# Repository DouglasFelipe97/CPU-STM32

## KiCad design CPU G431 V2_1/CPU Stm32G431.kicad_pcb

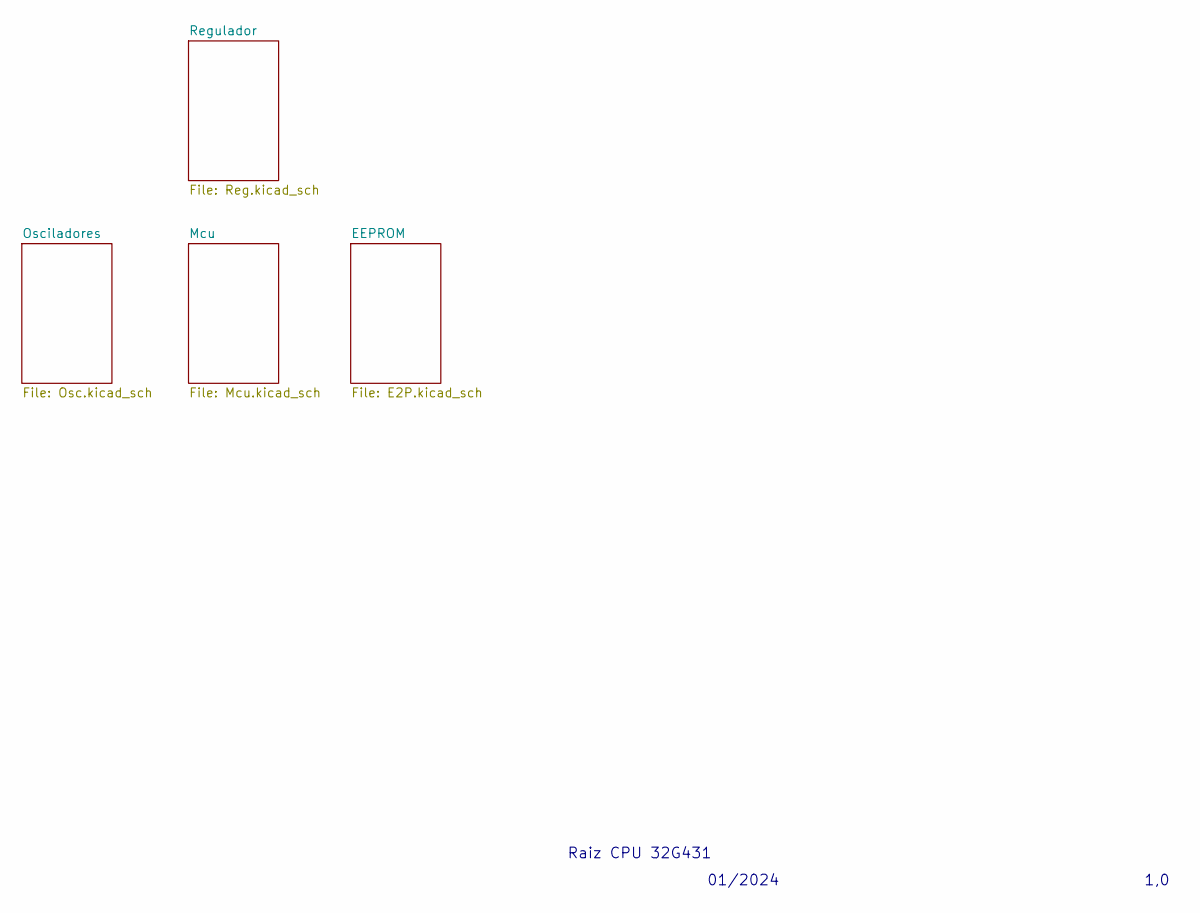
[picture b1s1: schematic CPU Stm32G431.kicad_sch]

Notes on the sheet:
Raiz CPU 32G431
01/2024
1,0

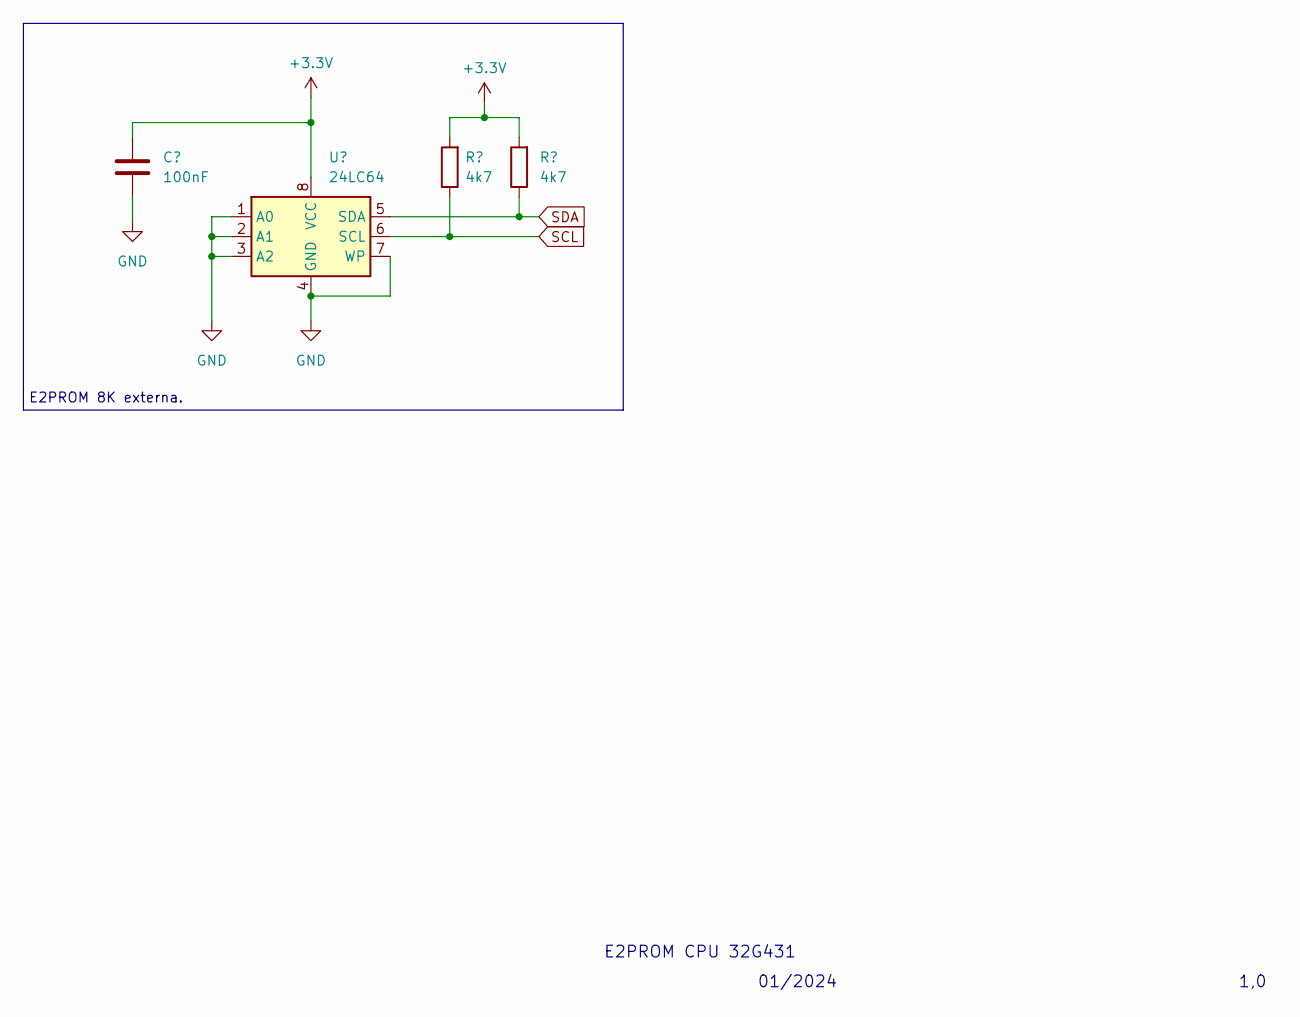
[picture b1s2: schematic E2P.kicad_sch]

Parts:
C6: 100nF; C_0805_2012Metric_Pad1.18x1.45mm_HandSolder
R6, R7: 4k7; R_0805_2012Metric_Pad1.20x1.40mm_HandSolder
U2: 24LC64; SOIC-8_3.9x4.9mm_P1.27mm

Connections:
GND: C6.1, U2.1 (A0), U2.2 (A1), U2.3 (A2), U2.4 (GND), U2.7 (WP); also elsewhere on the board
SCL: R6.1, U2.6 (SCL); also elsewhere on the board
SDA: R7.1, U2.5 (SDA); also elsewhere on the board
VDD: C6.2, R6.2, R7.2, U2.8 (VCC); also elsewhere on the board

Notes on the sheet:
E2PROM 8K externa.
E2PROM CPU 32G431
1,0
01/2024

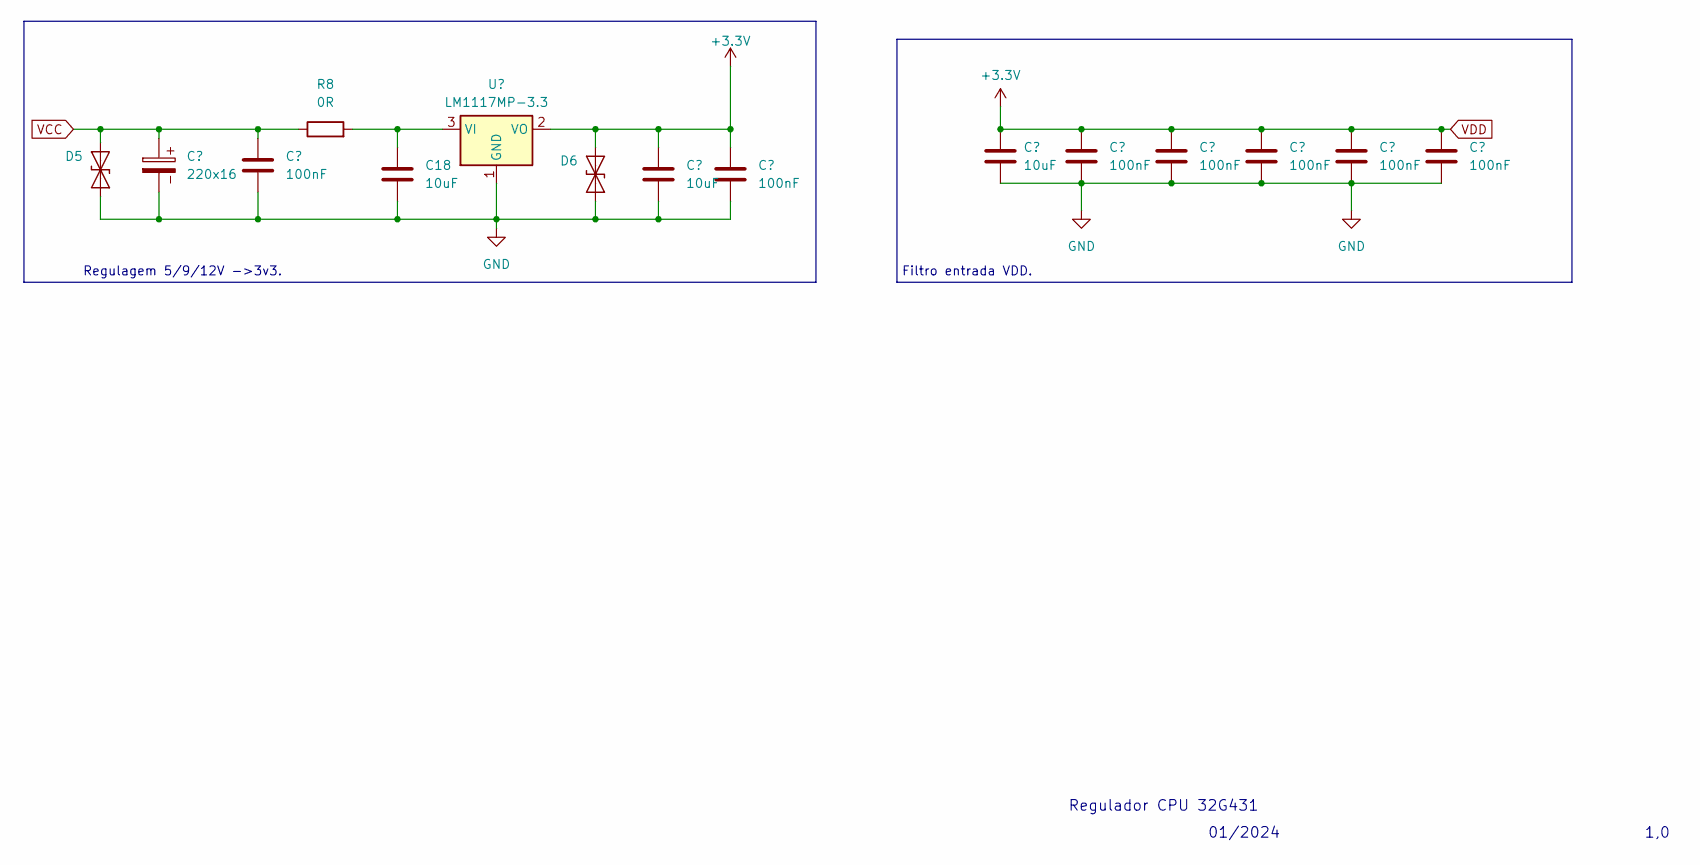
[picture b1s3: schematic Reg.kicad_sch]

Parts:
C7: 220x16; CP_Radial_D5.0mm_P2.50mm
C8, C10, C12, C13, C14, C15, C16: 100nF; C_0805_2012Metric_Pad1.18x1.45mm_HandSolder
C9, C11, C18: 10uF; C_0805_2012Metric_Pad1.18x1.45mm_HandSolder
D5: SMAJ6.5CA; D_SMA
D6: SMAJ6.5CA; D_MiniMELF
R8: 0R; R_0805_2012Metric_Pad1.20x1.40mm_HandSolder
U3: LM1117MP-3.3; SOT-223-3_TabPin2

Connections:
GND: C7.2, C8.1, C9.1, C10.1, C11.1, C12.1, C13.1, C14.1, C15.1, C16.1, C18.1, D5.1 (A1), D6.1 (A1), U3.1 (GND); also elsewhere on the board
unnamed: C18.2, R8.2, U3.3 (VI)
VCC: C7.1, C8.2, D5.2 (A2), R8.1; also elsewhere on the board
VDD: C9.2, C10.2, C11.2, C12.2, C13.2, C14.2, C15.2, C16.2, D6.2 (A2), U3.2 (VO); also elsewhere on the board

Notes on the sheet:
Regulagem 5/9/12V ->3v3.
01/2024
Regulador CPU 32G431
1,0
Filtro entrada VDD.

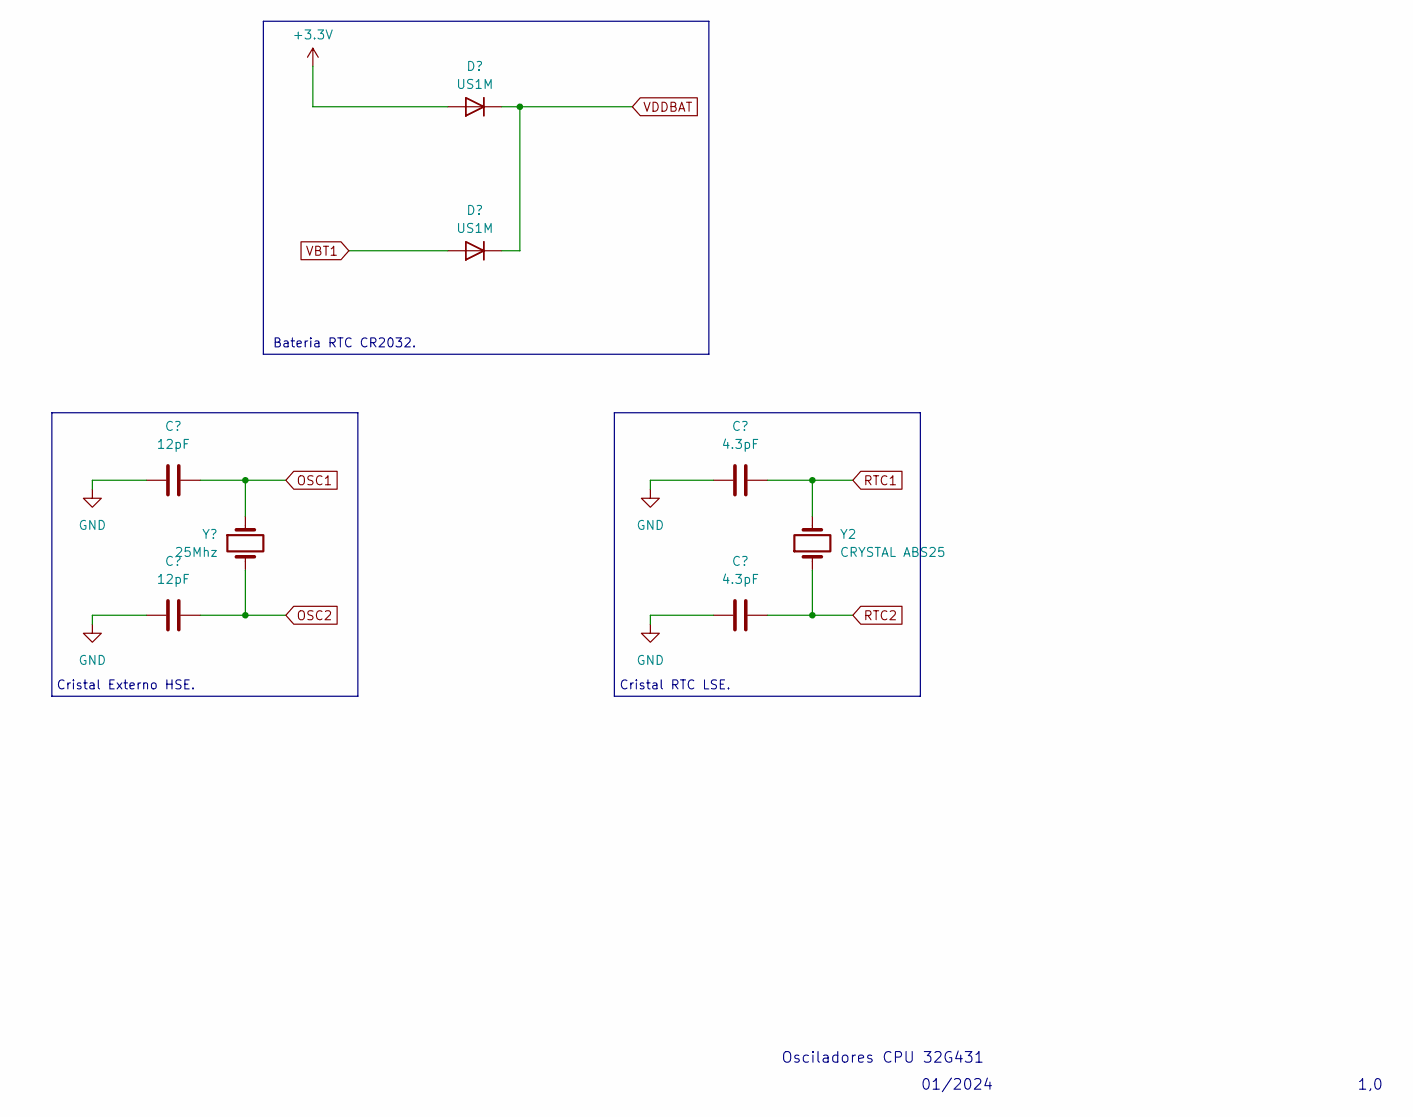
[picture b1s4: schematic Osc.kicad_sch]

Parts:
C2, C3: 12pF; C_0805_2012Metric_Pad1.18x1.45mm_HandSolder
C4, C5: 4.3pF; C_0805_2012Metric_Pad1.18x1.45mm_HandSolder
D3, D4: US1M; D_SMA
Y1: 25Mhz; Crystal_HC49-4H_Vertical
Y2: CRYSTAL ABS25; Crystal_SMD_Abracon_ABS25 Vertical

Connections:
GND: C2.1, C3.1, C4.1, C5.1; also elsewhere on the board
OSC1: C2.2, Y1.1; also elsewhere on the board
OSC2: C3.2, Y1.2; also elsewhere on the board
RTC1: C4.2, Y2.2; also elsewhere on the board
RTC2: C5.2, Y2.1; also elsewhere on the board
VBT1: D4.2 (A); also elsewhere on the board
VDD: D3.2 (A); also elsewhere on the board
VDDBAT: D3.1 (K), D4.1 (K); also elsewhere on the board

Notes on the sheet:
1,0
Cristal RTC LSE.
01/2024
Bateria RTC CR2032.
Cristal Externo HSE.
Osciladores CPU 32G431

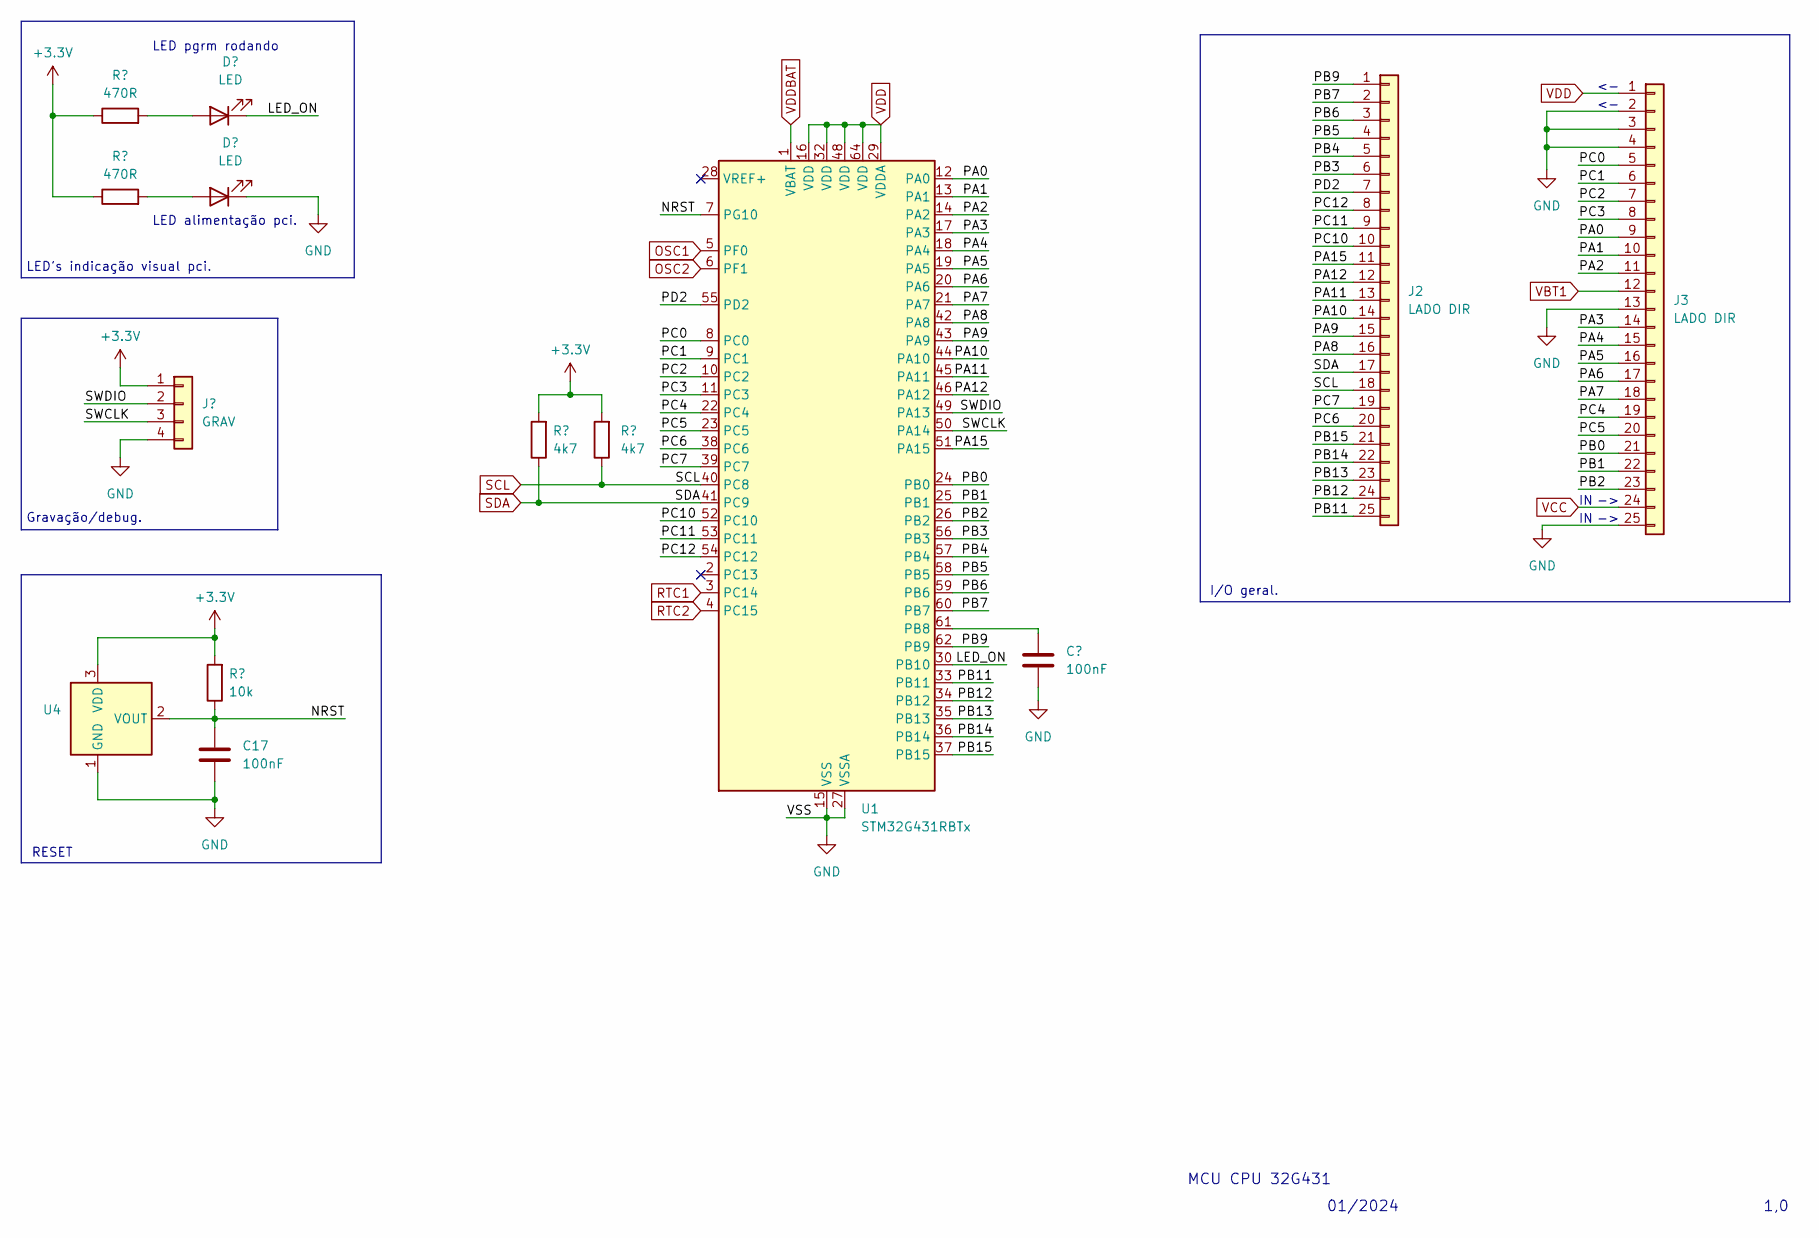
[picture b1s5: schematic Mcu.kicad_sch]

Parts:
C1, C17: 100nF; C_0805_2012Metric_Pad1.18x1.45mm_HandSolder
D1, D2: LED; LED_0805_2012Metric_Pad1.15x1.40mm_HandSolder
J1: GRAV; PinHeader_1x04_P2.54mm_Vertical
J2, J3: LADO DIR; PinHeader_1x25_P2.54mm_Vertical
R1: 10k; R_0805_2012Metric_Pad1.20x1.40mm_HandSolder
R2, R3: 470R; R_0805_2012Metric_Pad1.20x1.40mm_HandSolder
R4, R5: 4k7; R_0805_2012Metric_Pad1.20x1.40mm_HandSolder
U1: STM32G431RBTx; LQFP-64_10x10mm_P0.5mm
U4: BD48KxxG; SOT-23

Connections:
/Mcu/LED_ON: D1.1 (K), U1.30 (PB10)
/Mcu/NRST: C17.2, R1.1, U1.7 (PG10), U4.2 (VOUT)
/Mcu/PA0: J3.9, U1.12 (PA0)
/Mcu/PA1: J3.10, U1.13 (PA1)
/Mcu/PA2: J3.11, U1.14 (PA2)
/Mcu/PA3: J3.14, U1.17 (PA3)
/Mcu/PA4: J3.15, U1.18 (PA4)
/Mcu/PA5: J3.16, U1.19 (PA5)
/Mcu/PA6: J3.17, U1.20 (PA6)
/Mcu/PA7: J3.18, U1.21 (PA7)
/Mcu/PA8: J2.16, U1.42 (PA8)
/Mcu/PA9: J2.15, U1.43 (PA9)
/Mcu/PA10: J2.14, U1.44 (PA10)
/Mcu/PA11: J2.13, U1.45 (PA11)
/Mcu/PA12: J2.12, U1.46 (PA12)
/Mcu/PA15: J2.11, U1.51 (PA15)
/Mcu/PB0: J3.21, U1.24 (PB0)
/Mcu/PB1: J3.22, U1.25 (PB1)
/Mcu/PB2: J3.23, U1.26 (PB2)
/Mcu/PB3: J2.6, U1.56 (PB3)
/Mcu/PB4: J2.5, U1.57 (PB4)
/Mcu/PB5: J2.4, U1.58 (PB5)
/Mcu/PB6: J2.3, U1.59 (PB6)
/Mcu/PB7: J2.2, U1.60 (PB7)
/Mcu/PB9: J2.1, U1.62 (PB9)
/Mcu/PB11: J2.25, U1.33 (PB11)
/Mcu/PB12: J2.24, U1.34 (PB12)
/Mcu/PB13: J2.23, U1.35 (PB13)
/Mcu/PB14: J2.22, U1.36 (PB14)
/Mcu/PB15: J2.21, U1.37 (PB15)
/Mcu/PC0: J3.5, U1.8 (PC0)
/Mcu/PC1: J3.6, U1.9 (PC1)
/Mcu/PC2: J3.7, U1.10 (PC2)
/Mcu/PC3: J3.8, U1.11 (PC3)
/Mcu/PC4: J3.19, U1.22 (PC4)
/Mcu/PC5: J3.20, U1.23 (PC5)
/Mcu/PC6: J2.20, U1.38 (PC6)
/Mcu/PC7: J2.19, U1.39 (PC7)
/Mcu/PC10: J2.10, U1.52 (PC10)
/Mcu/PC11: J2.9, U1.53 (PC11)
/Mcu/PC12: J2.8, U1.54 (PC12)
/Mcu/PD2: J2.7, U1.55 (PD2)
/Mcu/SWCLK: J1.3, U1.50 (PA14)
/Mcu/SWDIO: J1.2, U1.49 (PA13)
GND: C1.1, C17.1, D2.1 (K), J1.4, J3.2, J3.3, J3.4, J3.13, J3.25, U1.15 (VSS), U1.27 (VSSA), U1.31 (VSS), U1.47 (VSS), U1.63 (VSS), U4.1 (GND); also elsewhere on the board
unnamed: D1.2 (A), R2.2
unnamed: D2.2 (A), R3.2
unnamed: C1.2, U1.61 (PB8)
OSC1: U1.5 (PF0); also elsewhere on the board
OSC2: U1.6 (PF1); also elsewhere on the board
RTC1: U1.3 (PC14); also elsewhere on the board
RTC2: U1.4 (PC15); also elsewhere on the board
SCL: J2.18, R5.1, U1.40 (PC8); also elsewhere on the board
SDA: J2.17, R4.1, U1.41 (PC9); also elsewhere on the board
VBT1: J3.12; also elsewhere on the board
VCC: J3.24; also elsewhere on the board
VDD: J1.1, J3.1, R1.2, R2.1, R3.1, R4.2, R5.2, U1.16 (VDD), U1.29 (VDDA), U1.32 (VDD), U1.48 (VDD), U1.64 (VDD), U4.3 (VDD); also elsewhere on the board
VDDBAT: U1.1 (VBAT); also elsewhere on the board

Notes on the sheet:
LED alimentação pci.
LED's indicação visual pci.
1,0
I/O geral.
01/2024
Gravação/debug.
LED pgrm rodando
RESET
MCU CPU 32G431

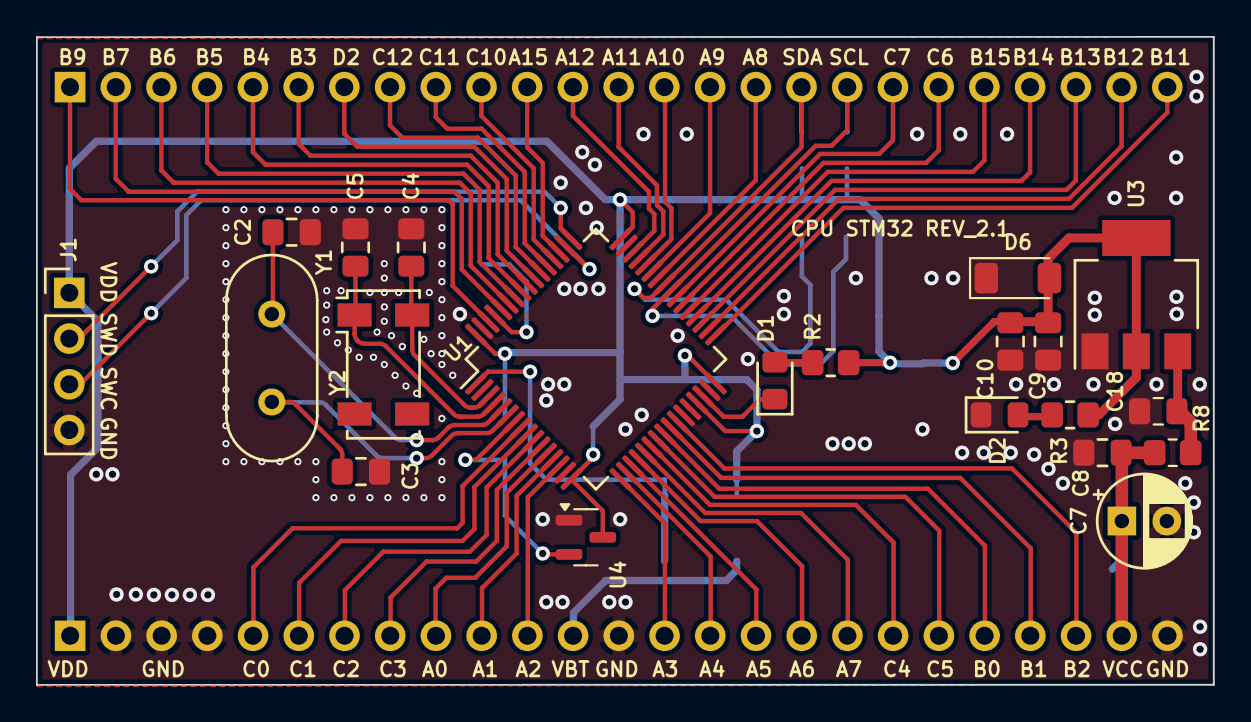
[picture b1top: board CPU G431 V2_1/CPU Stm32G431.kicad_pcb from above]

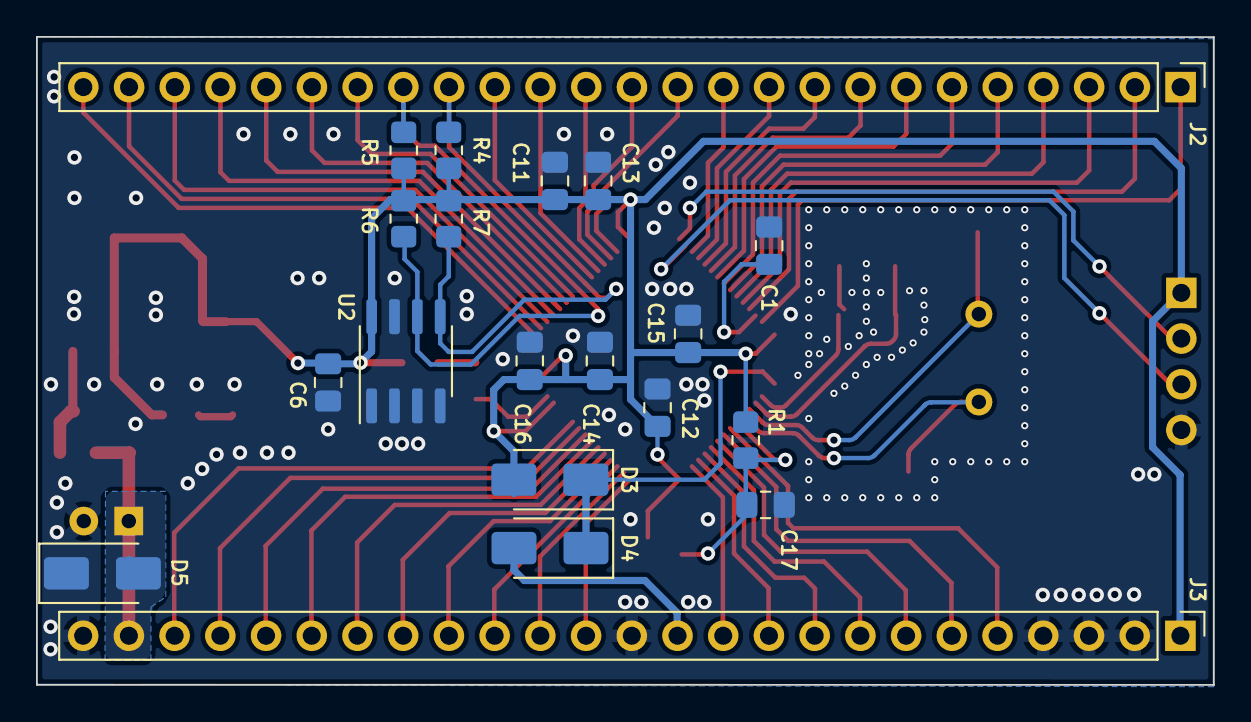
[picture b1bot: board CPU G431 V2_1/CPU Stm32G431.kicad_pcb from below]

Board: 2 copper layers, 65.4 x 36.0 mm, 41 parts (20 on the bottom side), 59 nets.

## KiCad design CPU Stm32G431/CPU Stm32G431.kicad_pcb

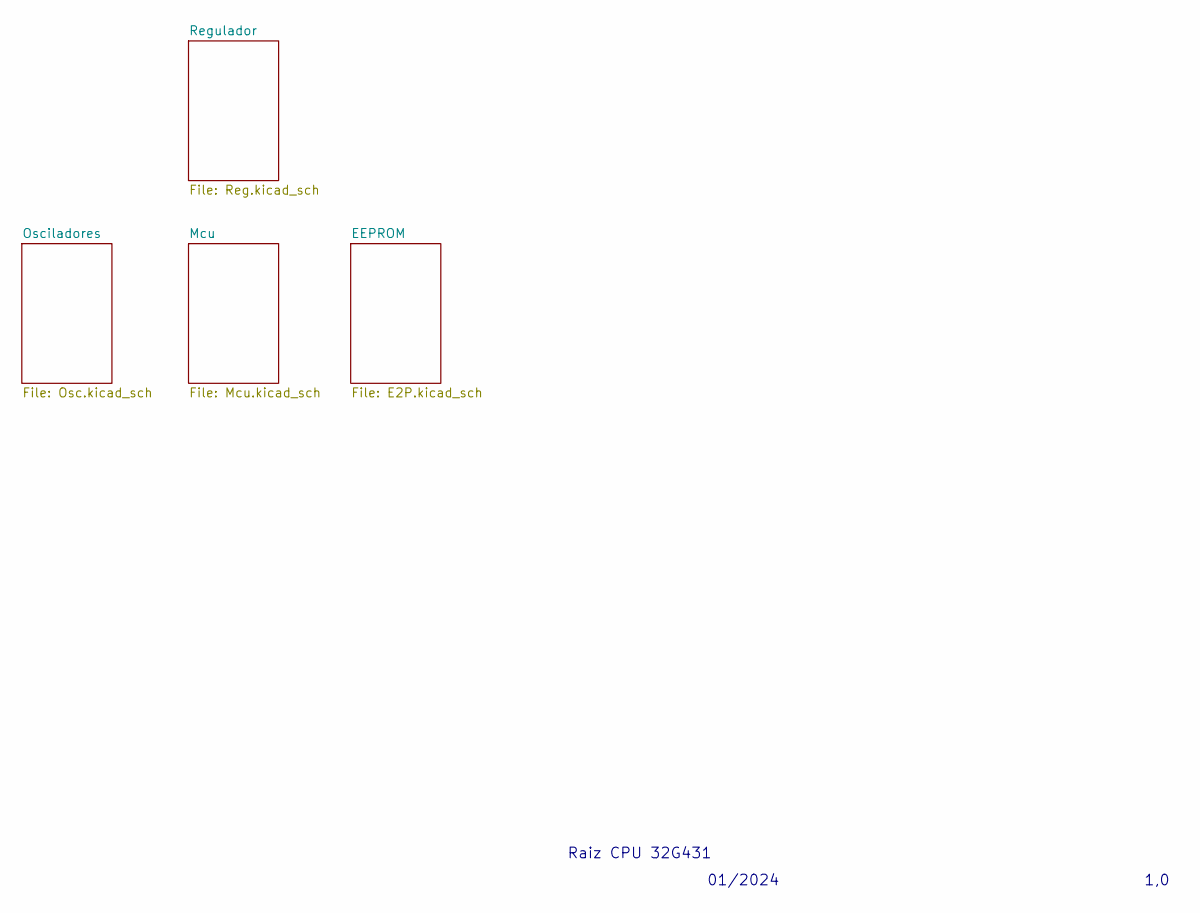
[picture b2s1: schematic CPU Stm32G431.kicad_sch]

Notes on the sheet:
Raiz CPU 32G431
01/2024
1,0

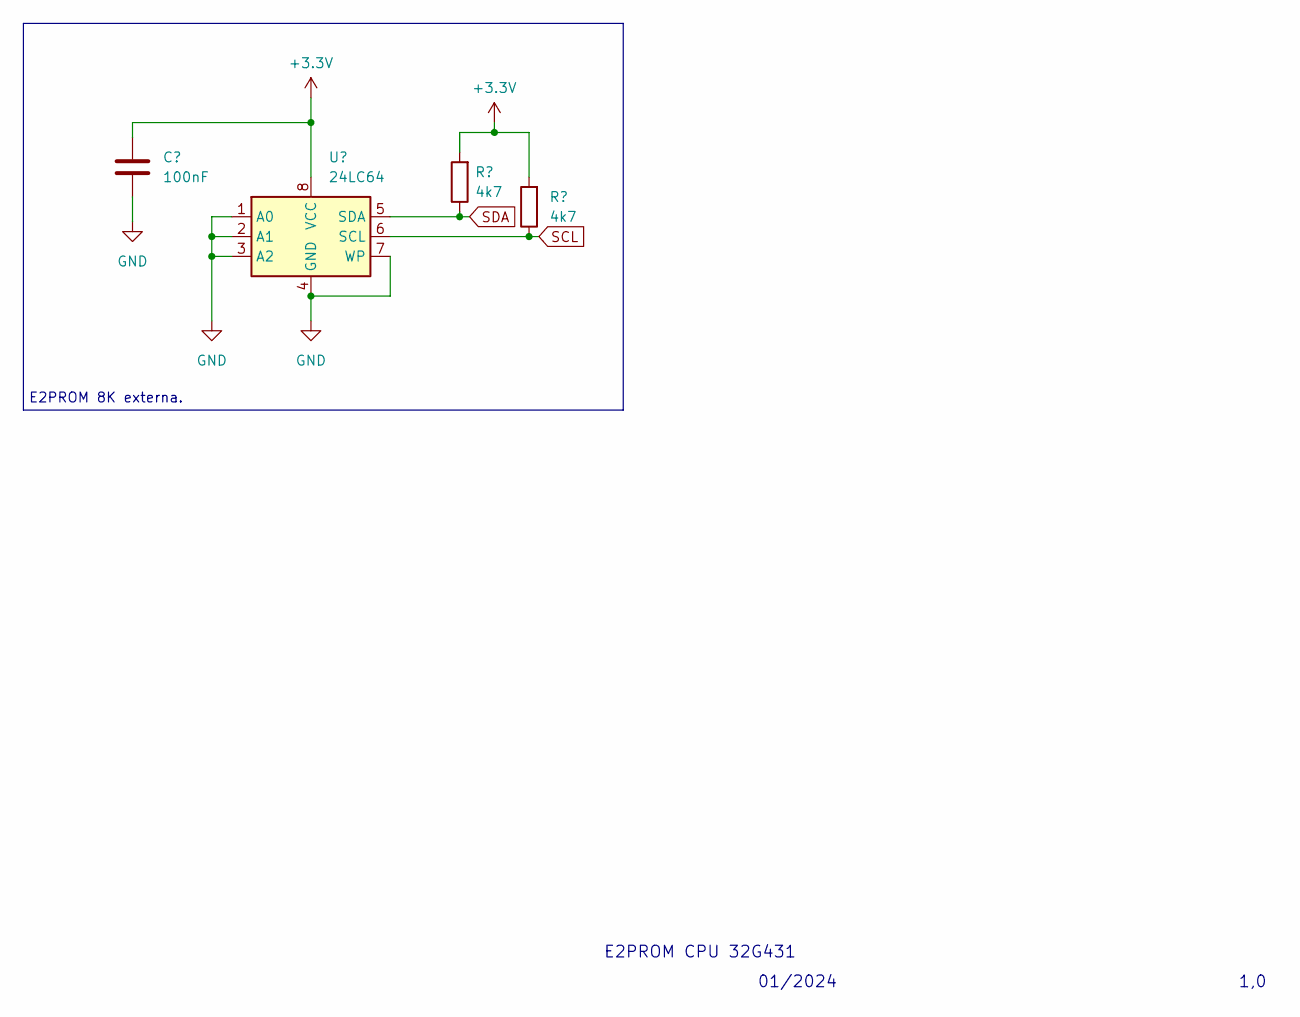
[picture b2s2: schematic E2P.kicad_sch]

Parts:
C17: 100nF; C_0805_2012Metric_Pad1.18x1.45mm_HandSolder
R4, R5: 4k7; R_0805_2012Metric_Pad1.20x1.40mm_HandSolder
U3: 24LC64; SOIC-8_3.9x4.9mm_P1.27mm

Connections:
GND: C17.1, U3.1 (A0), U3.2 (A1), U3.3 (A2), U3.4 (GND), U3.7 (WP); also elsewhere on the board
SCL: R5.1, U3.6 (SCL); also elsewhere on the board
SDA: R4.1, U3.5 (SDA); also elsewhere on the board
VDD: C17.2, R4.2, R5.2, U3.8 (VCC); also elsewhere on the board

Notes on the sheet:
E2PROM 8K externa.
E2PROM CPU 32G431
1,0
01/2024

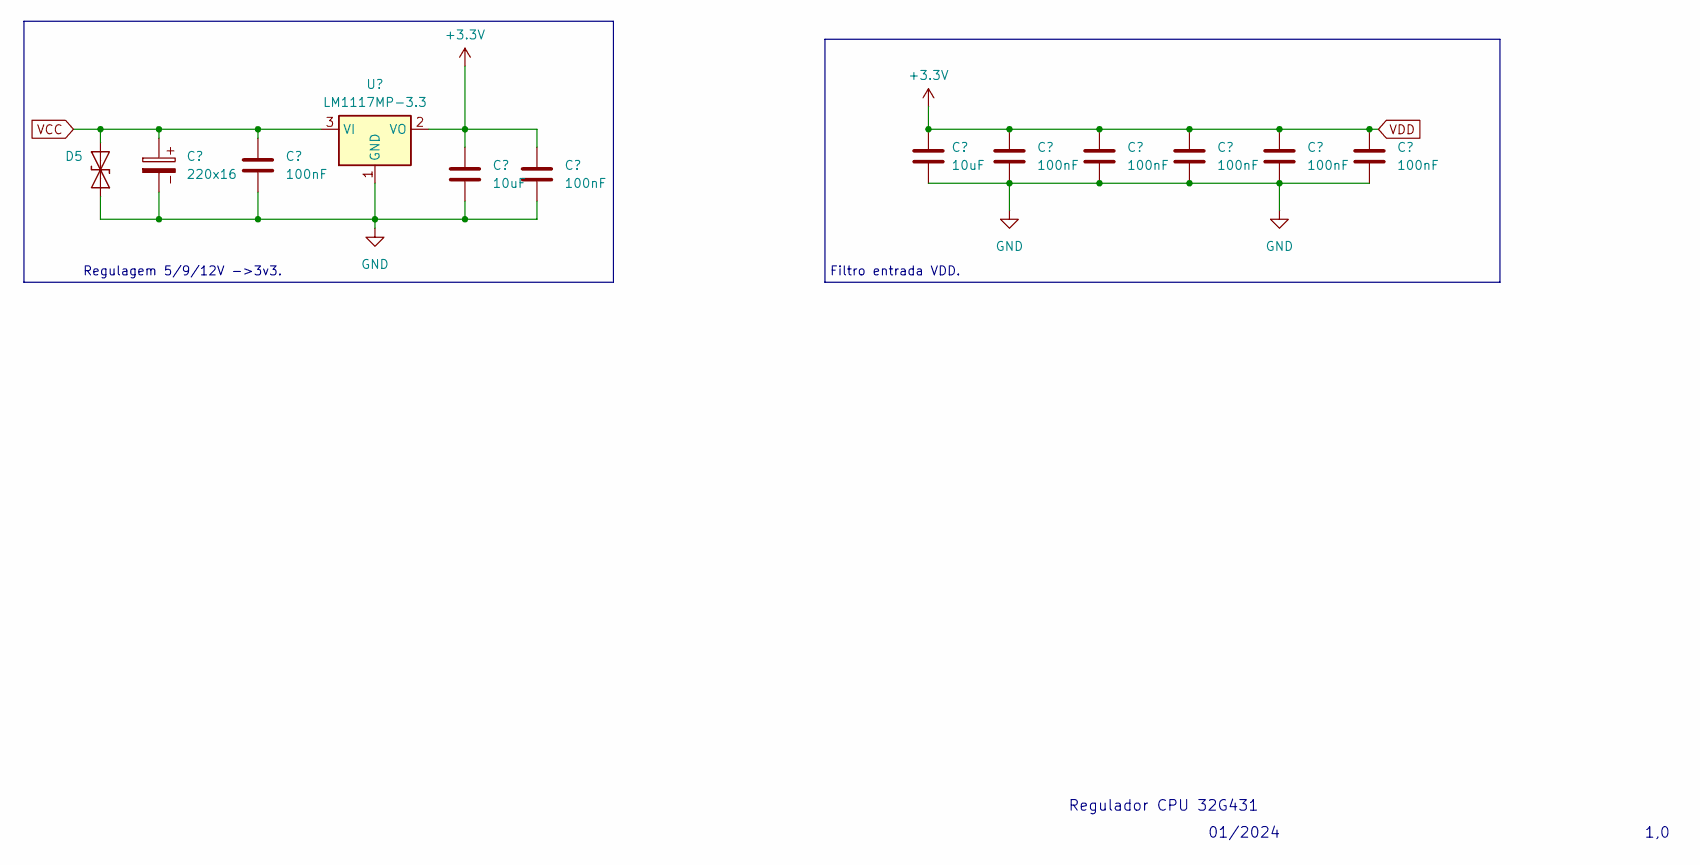
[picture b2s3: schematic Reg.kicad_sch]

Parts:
C5: 220x16; CP_Radial_D5.0mm_P2.50mm
C6, C8, C10, C11, C12, C13, C14: 100nF; C_0805_2012Metric_Pad1.18x1.45mm_HandSolder
C7, C9: 10uF; C_0805_2012Metric_Pad1.18x1.45mm_HandSolder
D5: SMAJ6.5CA; D_SMA
U1: LM1117MP-3.3; SOT-223-3_TabPin2

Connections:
GND: C5.2, C6.1, C7.1, C8.1, C9.1, C10.1, C11.1, C12.1, C13.1, C14.1, D5.1 (A1), U1.1 (GND); also elsewhere on the board
VCC: C5.1, C6.2, D5.2 (A2), U1.3 (VI); also elsewhere on the board
VDD: C7.2, C8.2, C9.2, C10.2, C11.2, C12.2, C13.2, C14.2, U1.2 (VO); also elsewhere on the board

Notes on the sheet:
Regulagem 5/9/12V ->3v3.
01/2024
Regulador CPU 32G431
1,0
Filtro entrada VDD.

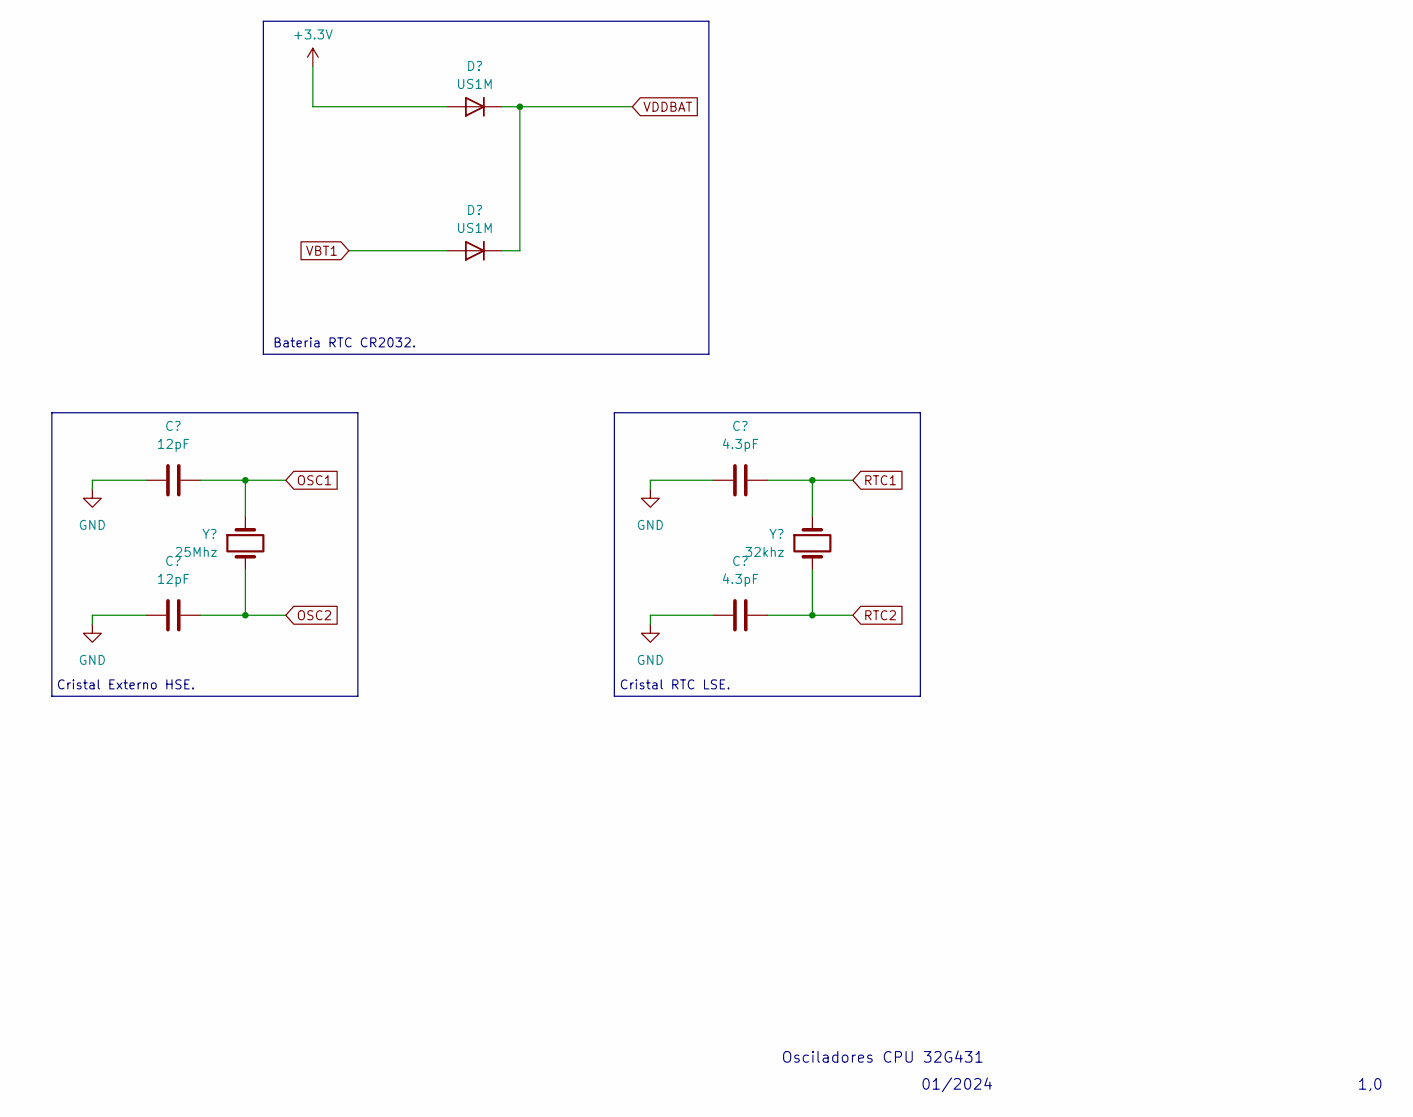
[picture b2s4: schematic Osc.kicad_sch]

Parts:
C1, C2: 12pF; C_0805_2012Metric_Pad1.18x1.45mm_HandSolder
C3, C4: 4.3pF; C_0805_2012Metric_Pad1.18x1.45mm_HandSolder
D1, D2: US1M; D_SMA
Y1: 25Mhz; Crystal_HC49-4H_Vertical
Y2: 32khz; Crystal_SMD_SeikoEpson_MC306-4Pin_8.0x3.2mm

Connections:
GND: C1.1, C2.1, C3.1, C4.1; also elsewhere on the board
OSC1: C1.2, Y1.1; also elsewhere on the board
OSC2: C2.2, Y1.2; also elsewhere on the board
RTC1: C3.2, Y2.1; also elsewhere on the board
RTC2: C4.2, Y2.2; also elsewhere on the board
VBT1: D2.2 (A); also elsewhere on the board
VDD: D1.2 (A); also elsewhere on the board
VDDBAT: D1.1 (K), D2.1 (K); also elsewhere on the board

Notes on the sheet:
1,0
Cristal RTC LSE.
01/2024
Bateria RTC CR2032.
Cristal Externo HSE.
Osciladores CPU 32G431

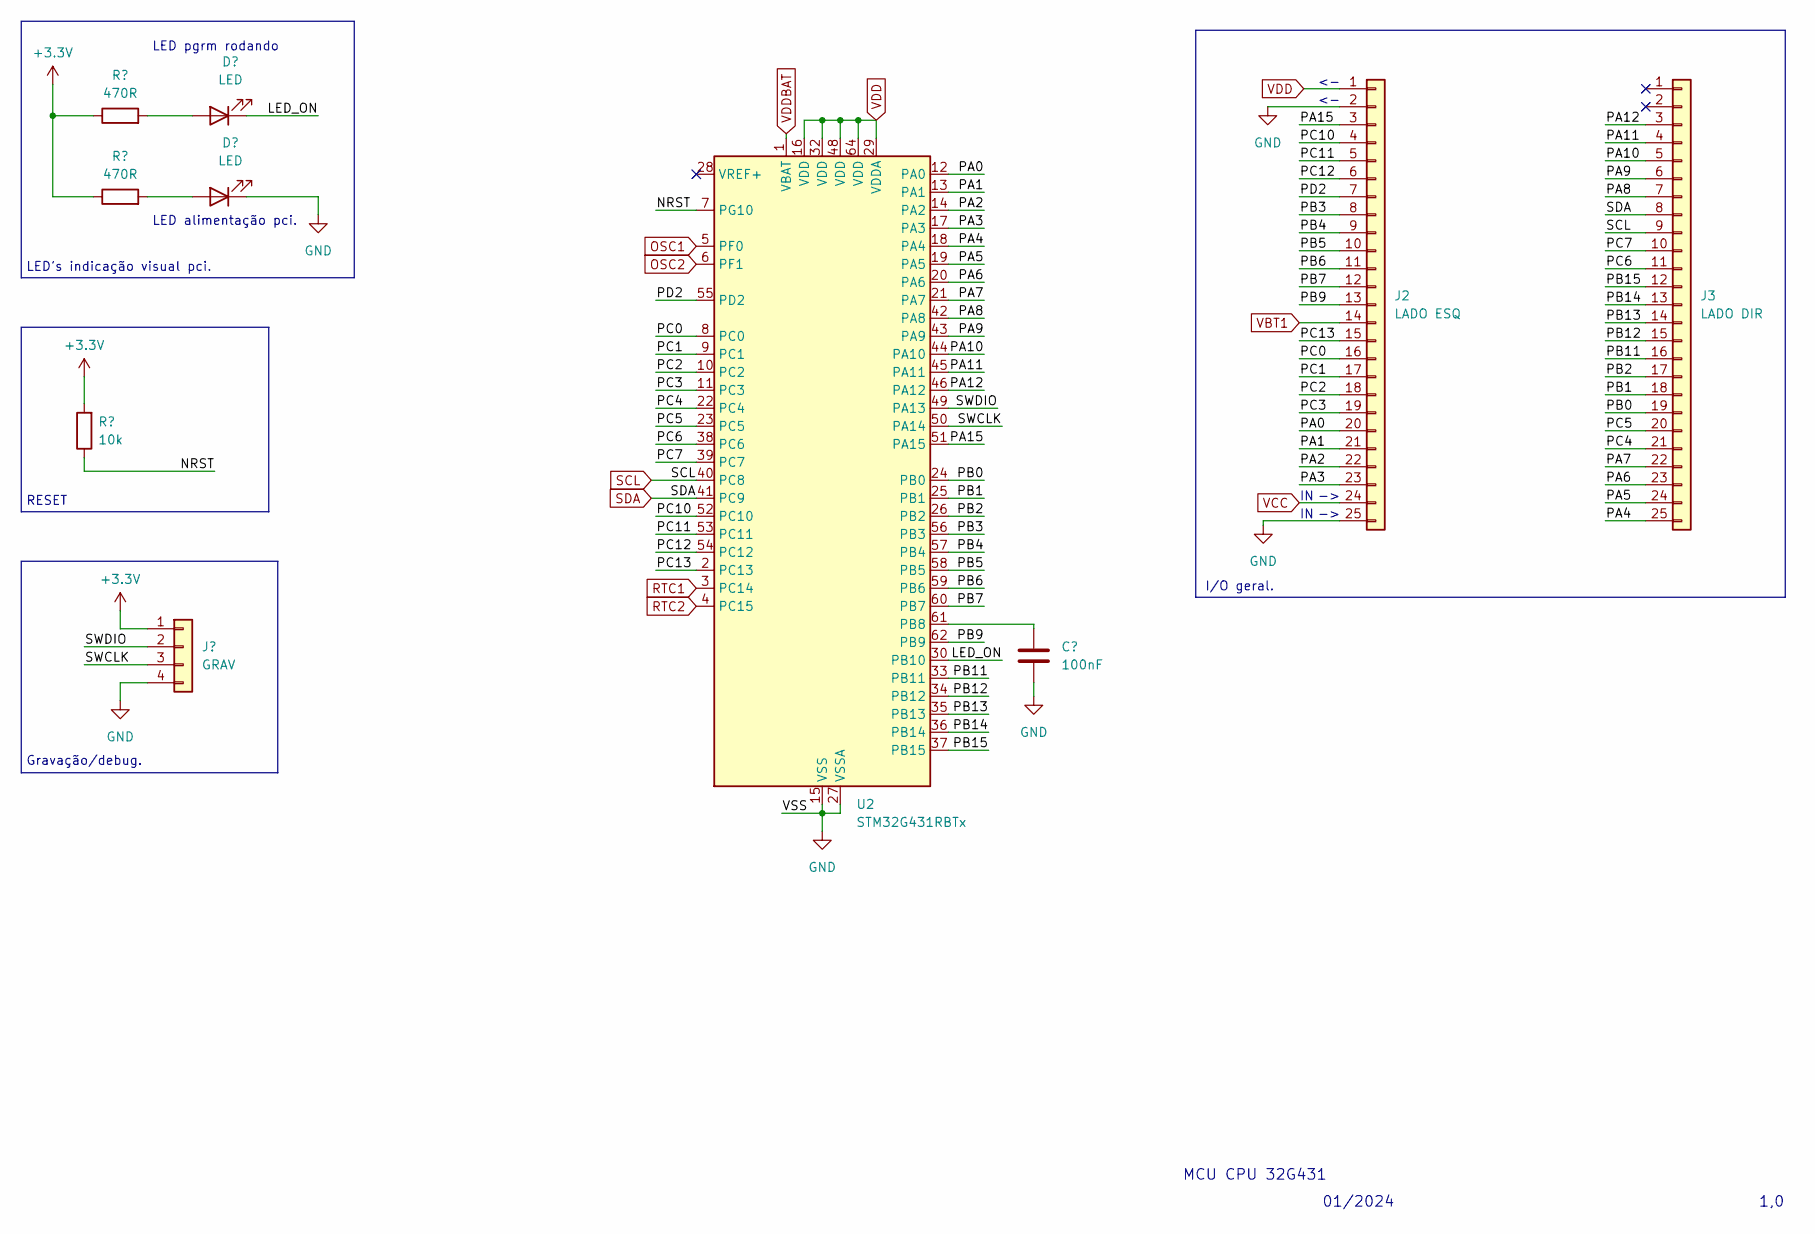
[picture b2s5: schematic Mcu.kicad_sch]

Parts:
C16: 100nF; C_0805_2012Metric_Pad1.18x1.45mm_HandSolder
D3, D4: LED; LED_0805_2012Metric_Pad1.15x1.40mm_HandSolder
J1: GRAV; PinHeader_1x04_P2.54mm_Vertical
J2: LADO ESQ; PinHeader_1x25_P2.54mm_Vertical
J3: LADO DIR; PinHeader_1x25_P2.54mm_Vertical
R1: 10k; R_0805_2012Metric_Pad1.20x1.40mm_HandSolder
R2, R3: 470R; R_0805_2012Metric_Pad1.20x1.40mm_HandSolder
U2: STM32G431RBTx; LQFP-64_10x10mm_P0.5mm

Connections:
/Mcu/LED_ON: D3.1 (K), U2.30 (PB10)
/Mcu/NRST: R1.1, U2.7 (PG10)
/Mcu/PA0: J2.20, U2.12 (PA0)
/Mcu/PA1: J2.21, U2.13 (PA1)
/Mcu/PA2: J2.22, U2.14 (PA2)
/Mcu/PA3: J2.23, U2.17 (PA3)
/Mcu/PA4: J3.25, U2.18 (PA4)
/Mcu/PA5: J3.24, U2.19 (PA5)
/Mcu/PA6: J3.23, U2.20 (PA6)
/Mcu/PA7: J3.22, U2.21 (PA7)
/Mcu/PA8: J3.7, U2.42 (PA8)
/Mcu/PA9: J3.6, U2.43 (PA9)
/Mcu/PA10: J3.5, U2.44 (PA10)
/Mcu/PA11: J3.4, U2.45 (PA11)
/Mcu/PA12: J3.3, U2.46 (PA12)
/Mcu/PA15: J2.3, U2.51 (PA15)
/Mcu/PB0: J3.19, U2.24 (PB0)
/Mcu/PB1: J3.18, U2.25 (PB1)
/Mcu/PB2: J3.17, U2.26 (PB2)
/Mcu/PB3: J2.8, U2.56 (PB3)
/Mcu/PB4: J2.9, U2.57 (PB4)
/Mcu/PB5: J2.10, U2.58 (PB5)
/Mcu/PB6: J2.11, U2.59 (PB6)
/Mcu/PB7: J2.12, U2.60 (PB7)
/Mcu/PB9: J2.13, U2.62 (PB9)
/Mcu/PB11: J3.16, U2.33 (PB11)
/Mcu/PB12: J3.15, U2.34 (PB12)
/Mcu/PB13: J3.14, U2.35 (PB13)
/Mcu/PB14: J3.13, U2.36 (PB14)
/Mcu/PB15: J3.12, U2.37 (PB15)
/Mcu/PC0: J2.16, U2.8 (PC0)
/Mcu/PC1: J2.17, U2.9 (PC1)
/Mcu/PC2: J2.18, U2.10 (PC2)
/Mcu/PC3: J2.19, U2.11 (PC3)
/Mcu/PC4: J3.21, U2.22 (PC4)
/Mcu/PC5: J3.20, U2.23 (PC5)
/Mcu/PC6: J3.11, U2.38 (PC6)
/Mcu/PC7: J3.10, U2.39 (PC7)
/Mcu/PC10: J2.4, U2.52 (PC10)
/Mcu/PC11: J2.5, U2.53 (PC11)
/Mcu/PC12: J2.6, U2.54 (PC12)
/Mcu/PC13: J2.15, U2.2 (PC13)
/Mcu/PD2: J2.7, U2.55 (PD2)
/Mcu/SWCLK: J1.3, U2.50 (PA14)
/Mcu/SWDIO: J1.2, U2.49 (PA13)
GND: C16.1, D4.1 (K), J1.4, J2.2, J2.25, U2.15 (VSS), U2.27 (VSSA), U2.31 (VSS), U2.47 (VSS), U2.63 (VSS); also elsewhere on the board
unnamed: D3.2 (A), R2.2
unnamed: D4.2 (A), R3.2
unnamed: C16.2, U2.61 (PB8)
OSC1: U2.5 (PF0); also elsewhere on the board
OSC2: U2.6 (PF1); also elsewhere on the board
RTC1: U2.3 (PC14); also elsewhere on the board
RTC2: U2.4 (PC15); also elsewhere on the board
SCL: J3.9, U2.40 (PC8); also elsewhere on the board
SDA: J3.8, U2.41 (PC9); also elsewhere on the board
VBT1: J2.14; also elsewhere on the board
VCC: J2.24; also elsewhere on the board
VDD: J1.1, J2.1, R1.2, R2.1, R3.1, U2.16 (VDD), U2.29 (VDDA), U2.32 (VDD), U2.48 (VDD), U2.64 (VDD); also elsewhere on the board
VDDBAT: U2.1 (VBAT); also elsewhere on the board

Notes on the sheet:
LED alimentação pci.
LED's indicação visual pci.
1,0
I/O geral.
01/2024
Gravação/debug.
LED pgrm rodando
RESET
MCU CPU 32G431
